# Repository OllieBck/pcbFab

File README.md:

# pcbFab

Eagle Files -- still needs work

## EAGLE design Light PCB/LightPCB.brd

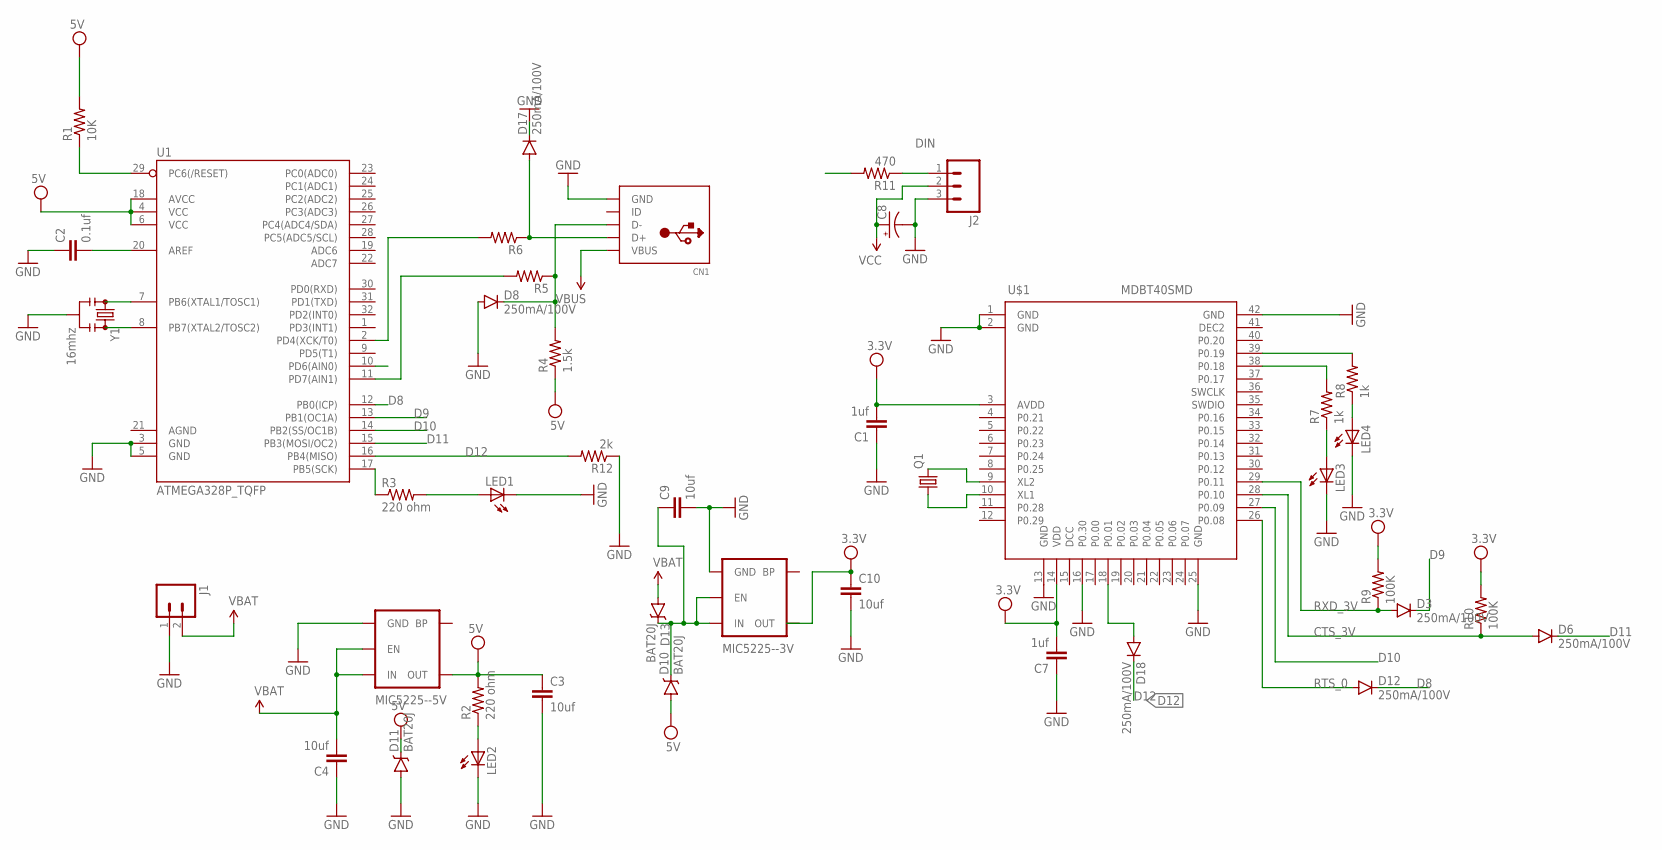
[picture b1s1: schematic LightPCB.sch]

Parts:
C1, C7: 1uf; 0603-CAP
C2: 0.1uf; 0603-CAP
C3, C4, C9, C10: 10uf; 0603-CAP
C8: CAP_POLPTH4; CPOL-RADIAL-1000UF-25V
CN1: USBMINIB; USB-MINIB
D3, D6, D8, D12, D17, D18: 250mA/100V; SOD-323
D10, D11, D13: BAT20J; SOD-323
J1: M02LOCK_LONGPADS; 1X02_LOCK_LONGPADS
J2: M03PTH; 1X03
LED1, LED2, LED3, LED4: LEDCHIPLED_0603; CHIPLED_0603
MIC5225--3V, MIC5225--5V: MIC52055V; SOT23-5
Q1: CRYSTALMM20SS; MM20SS
R1: 10K; 0603-RES
R2, R3: 220 ohm; 0603-RES
R4: 1.5k; 0603-RES
R5, R6: RESISTOR0603-RES; 0603-RES
R7, R8: 1k; 0603-RES
R9, R10: 100K; 0603-RES
R11: 470; 0603-RES
R12: 2k; 0603-RES
U1: ATMEGA328P_TQFP; TQFP32-08
U$1: MDBT40SMD; MDBT40
Y1: 16mhz; RESONATOR-SMD_MED

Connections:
3V: C1.2, C7.2, R10.2, U$1.3 (AVDD), U$1.14 (VDD)
5V: U1.4 (VCC), U1.6 (VCC), U1.18 (AVCC)
CTS_3V: D6.A, R10.1, U$1.28 (P0.10)
D6: R11.2, U1.10 (PD6(AIN0))
D8: D12.C, U1.12 (PB0(ICP))
D9: D3.C, U1.13 (PB1(OC1A))
D10: U1.14 (PB2(SS/OC1B)), U$1.27 (P0.09)
D11: D6.C, U1.15 (PB3(MOSI/OC2))
D12: D18.C, R12.2, U1.16 (PB4(MISO))
DIN: J2.1, R11.1
GND: C1.1, C2.1, C3.2, C4.1, C7.1, C8.-, C9.2, C10.2, CN1.GND, D8.A, D11.A, D17.C, J1.1, J2.3, LED1.C, LED2.C, LED3.C, LED4.C, MIC5225--3V.2 (GND), MIC5225--5V.2 (GND), R12.1, U1.3 (GND), U1.5 (GND), U$1.1 (GND), U$1.2 (GND), U$1.13 (GND), U$1.16 (P0.30), U$1.25 (GND), U$1.42 (GND), Y1.2
unnamed: C2.2, U1.20 (AREF)
unnamed: U1.8 (PB7(XTAL2/TOSC2)), Y1.3
unnamed: R1.1, U1.29 (PC6(/RESET))
unnamed: U1.7 (PB6(XTAL1/TOSC1)), Y1.1
unnamed: R5.2, U1.11 (PD7(AIN1))
unnamed: CN1.D-, D8.C, R4.2, R5.1
unnamed: CN1.D+, D17.A, R6.1
unnamed: R6.2, U1.2 (PD4(XCK/T0))
unnamed: R3.1, U1.17 (PB5(SCK))
unnamed: LED1.A, R3.2
unnamed: LED2.A, R2.1
unnamed: Q1.4 (2), U$1.9 (XL2)
unnamed: Q1.1, U$1.10 (XL1)
unnamed: LED3.A, R7.1
unnamed: LED4.A, R8.1
unnamed: R8.2, U$1.39 (P0.19)
unnamed: R7.2, U$1.38 (P0.18)
unnamed: D18.A, U$1.18 (P0.01)
unnamed: C9.1, D10.C, D13.C, MIC5225--3V.1 (IN), MIC5225--3V.3 (EN)
RTS_0: D12.A, U$1.26 (P0.08)
RXD_3V: D3.A, R9.1, U$1.29 (P0.11)
VCC: C3.1, C8.+, C10.1, CN1.VBUS, D10.A, D11.C, J2.2, MIC5225--5V.5 (OUT), R1.2, R2.2, R4.1, R9.2
VIN: C4.2, D13.A, J1.2, MIC5225--5V.1 (IN), MIC5225--5V.3 (EN)

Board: 2 copper layers, 42 parts (0 on the bottom side), 34 nets, no tracks yet.

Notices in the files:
parts and their libraries:
SparkFun-Capacitors: Licensing: Creative Commons ShareAlike 4.0 International - https://creativecommons.org/licenses/by-sa/4.0
